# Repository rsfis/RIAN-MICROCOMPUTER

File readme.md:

<h1 align="center">
  Fiscion Razor32
</h1>
<h3 align="center">
  A Mini Foldable OldStyle Computer
</h3>

<h3 align="center">
  Being only 14x6x5cm, Razor32 is a complete computer with Firmware, OS and Apps.
</h3>

## Features
- Powered by ESP32 S3 Chip with 8mb RAM and 16mb Flash
- Embedded TFT Screen
- 30 keys Matricial Keyboard. Each key has X and Y push up output
- 3000mah Rechargeable Battery
- Foldable Case Easy and Light to Carry
- USB C charging port
- Easy to assemble
- Custom Firmware and OS
- Runs LUA for Apps
- Easy to create your own apps in a Inside IDE and share them within a local network

## Case
Designed using Blender, the Case comes with 4 parts: The lower box, upper box, hinges and screws. Made using PLA material.

## PCB
The PCBs were made using KiCad. The board contains the sockets for esp32 and screen and a 3x10 matricial keyboard using push buttons.

F.Cu

In.1.Cu

In.2.Cu

B.Cu

3D render front

3D render back

Schematic

#### External Wiring Diagram

## BOM
|FIELD1|Designator                                  |Quantity|Comment                                                                                                       |Link                                                                                                                                       |ENTIRE PRICE WITH FREIGHT AND TAXES:|FIELD7|FIELD8|FIELD9|
|------|--------------------------------------------|--------|--------------------------------------------------------------------------------------------------------------|-------------------------------------------------------------------------------------------------------------------------------------------|------------------------------------|------|------|------|
|1     |TFT Screen 3.5" st7796 320*480 ips          |1       |TFT Screen 3.5" st7796 320*480 ips Touch                                                                      |https://pt.aliexpress.com/item/1005005995931721.html?spm=a2g0o.order_list.order_list_main.31.288ecaa4EGynx2&gatewayAdapt=glo2bra           |R$ 90,84                            |      |      |      |
|2     |ESP32 S3 8mb PSRAM 16mb Flash               |1       |ESP32-S3-DevKitC-1                                                                                            |https://pt.aliexpress.com/item/1005007215982839.html?spm=a2g0o.order_list.order_list_main.46.288ecaa4EGynx2&gatewayAdapt=glo2bra           |R$ 63,38                            |      |      |      |
|3     |Aliexpress parts                            |1       |Pin Headers 1x15 and 1x6; Flat Cable Socket Bottom Connector 14pins; Screws M3x6mm Allen; Push Buttons 6x6x5mm|(Cart image at repo: cart/aliexpress.png)                                                                                                  |R$ 129,76                           |      |      |      |
|4     |3D Print                                    |2       |3D Print Case                                                                                                 |~                                                                                                                                          |~                                   |      |      |      |
|5     |PCB                                         |5       |PCB Manufacture Process                                                                                       |~                                                                                                                                          |$36,35                              |      |      |PRICE |
|6     |Battery 3.7v 3000mah                        |1       |Battery 3000mah 3.7v                                                                                          |https://www.mercadolivre.com.br/1-unidade-505573-2-fios-3000mah-37v-5mm-x-55mm-x-73mm/p/MLB2081347995?pdp_filters=item_id:MLB1929447427    |$12,00                              |      |R$    |552,13|
|7     |Battery Charger Module and Step Up Conversor|1       |Battery Charger Module and Step Up 3.7v to 5v Conversor                                                       |https://www.mercadolivre.com.br/carregador-bateria-de-litio-5v-2a-conversor-step-up-usb-c/p/MLB2071876811?pdp_filters=item_id:MLB4418035779|$3,42                               |      |USD   |106,59|

## Keyboard Keys Organization
q w e r t y u i o p

a s d f g h j k l B

z x c v b S n m f E

1 2 3 4 5 6 7 8 9 0

+ - % < > ? & ! ( )

/ * = " _ ; . , f Sh

ESC F1 F2 F3 F4 F5 F6 F7 F8 F9

{    }  @ :  [  ]  

|    \  ' -  HOME

## OS and APPS
The OS is the RazorOS, made using ArduinoIDE, LovyanGFX and LUA Interpreter.

The OS itself is programmed in C++ using Arduino IDE, with own firmware. The OS has:
- Home Page with a Desktop area
- Control Panel for Rapid Settings
- Users
- Clock
- Settings
- Task Manager
- Notifications
- Watchdog
- Terminal in LUA

The apps are made in LUA. Apps will create a LUA Virtual Machine to execute the code directly in the processor using various C++ External Functions. 

Using the Text Editor, you will also be able to create your own apps to Razor32 and control everything.

Planned Apps:
- Internet Browser Based on Text (Lynx)
- File Sender

- Text Editor
- Calculator
- To-do
- Calendar
- PDF Viewer
- Excel Like

- Tetris
- Snake

- Scanner Wifi
- Terminal Serial
- Packet Logger

OS and Firmware are still being programmed. For now, RazorOS already has basic drawing and OS functions and Lua VM implemented.

## Cart

## Getting Started
### How to flash the ESP32:
- Install ArduinoIDE
- Install the following libraries:
-- LovyanGFX, by lovyan03
-- ArduinoJSON, by BenoitBlanchon
- Install the following Board Managers:
-- esp32, by Espressif Systems
-- Select the COM and board 4D Systems gen4-ESP32 Modules (ESP32-S3)
### Extract the files from /firmware/MicroSD Backup.rar
- Copy the files from /firmware/MicroSD Backup.rar to the microsd root directory
- Insert the micro sd in the MicroSD socket below the screen

Made for: Hackclub FORGE - https://forge.hackclub.com/projects/457

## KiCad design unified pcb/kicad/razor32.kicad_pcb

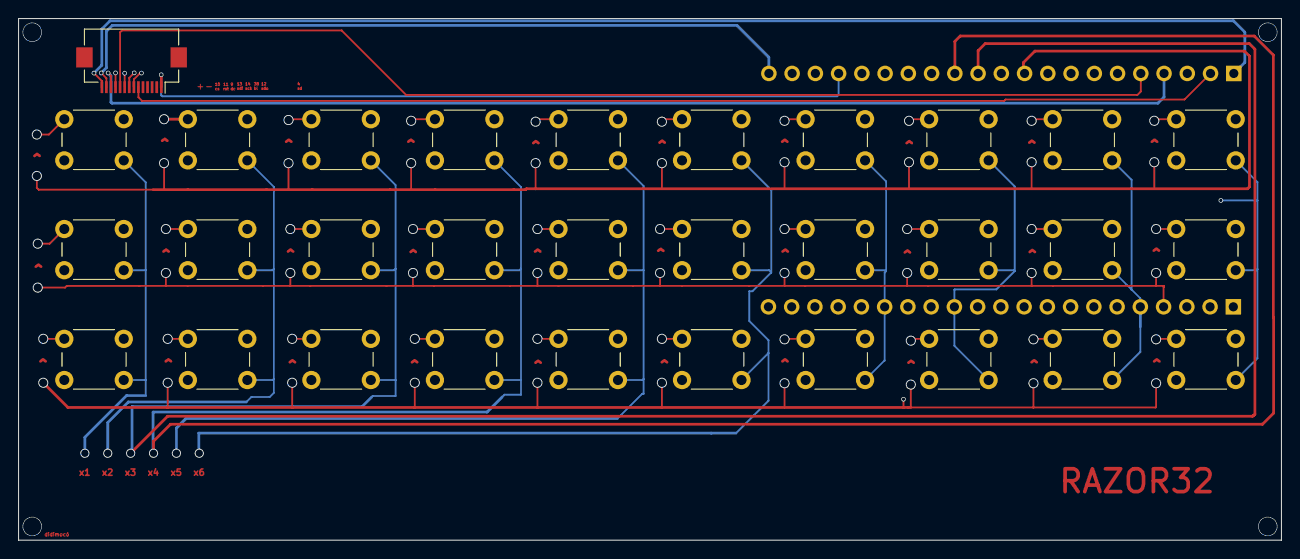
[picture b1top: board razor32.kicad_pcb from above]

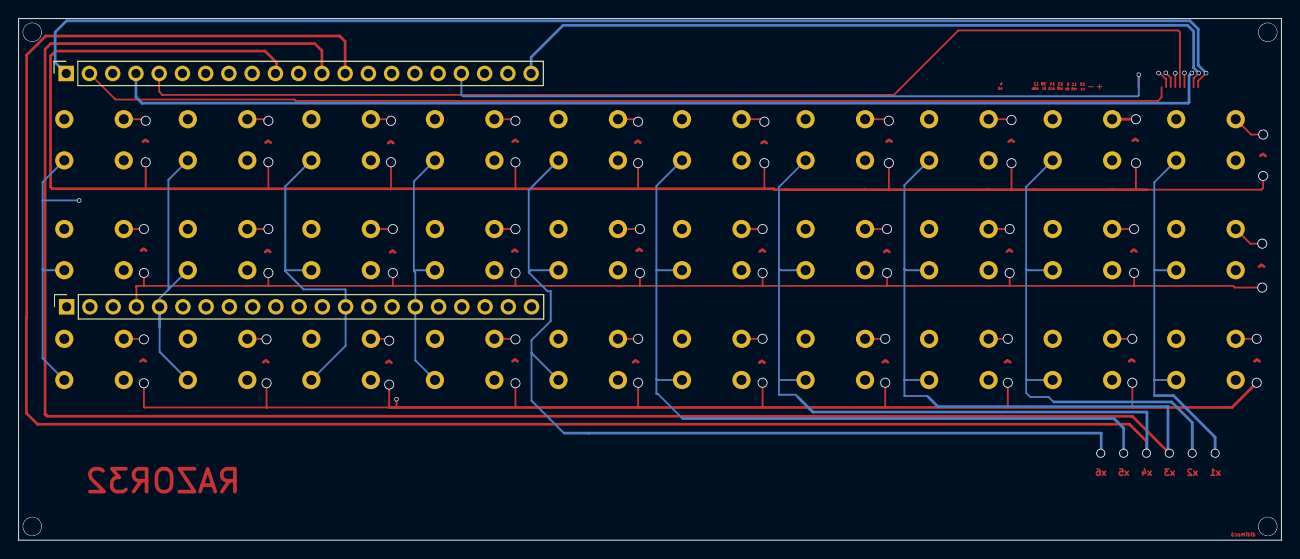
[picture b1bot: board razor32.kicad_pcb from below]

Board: 4 copper layers, 138.0 x 57.0 mm, 33 parts (2 on the bottom side), 23 nets.

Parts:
ESP32PinSocket_1, ESP32PinSocket_2: PinSocket_1x21_P2.54mm_Vertical
FlatCableSocket: Hirose_FH12-14S-0.5SH_1x14-1MP_P0.50mm_Horizontal
a: SW_PUSH_6mm
b: SW_PUSH_6mm
c: SW_PUSH_6mm
d: SW_PUSH_6mm
e: SW_PUSH_6mm
enter: SW_PUSH_6mm
f: SW_PUSH_6mm
fun: SW_PUSH_6mm
g: SW_PUSH_6mm
h: SW_PUSH_6mm
i: SW_PUSH_6mm
j: SW_PUSH_6mm
k: SW_PUSH_6mm
l: SW_PUSH_6mm
m: SW_PUSH_6mm
n: SW_PUSH_6mm
o: SW_PUSH_6mm
p: SW_PUSH_6mm
q: SW_PUSH_6mm
r: SW_PUSH_6mm
ret: SW_PUSH_6mm
s: SW_PUSH_6mm
space: SW_PUSH_6mm
t: SW_PUSH_6mm
u: SW_PUSH_6mm
v: SW_PUSH_6mm
w: SW_PUSH_6mm
x: SW_PUSH_6mm
y: SW_PUSH_6mm
z: SW_PUSH_6mm

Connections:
bl: ESP32PinSocket_2.12, FlatCableSocket.7
cs: ESP32PinSocket_1.4, FlatCableSocket.12
dc: ESP32PinSocket_1.5, FlatCableSocket.10
rst: ESP32PinSocket_1.3, FlatCableSocket.11
sck: ESP32PinSocket_2.3, FlatCableSocket.8
sd: ESP32PinSocket_1.18, FlatCableSocket.1
sdi: ESP32PinSocket_2.2, FlatCableSocket.9
sdo: ESP32PinSocket_1.2, FlatCableSocket.6
sgnd: ESP32PinSocket_1.21, FlatCableSocket.13
vcc: ESP32PinSocket_1.1, FlatCableSocket.14
x1: ESP32PinSocket_2.6, a.2, q.2, z.2
x2: ESP32PinSocket_2.7, s.2, w.2, x.2
x3: ESP32PinSocket_1.12, c.2, d.2, e.2
x4: ESP32PinSocket_1.13, f.2, r.2, v.2
x5: ESP32PinSocket_2.14, b.2, g.2, t.2
x6: ESP32PinSocket_1.11, h.2, space.2, y.2
x7: ESP32PinSocket_2.16, j.2, n.2, u.2
x8: ESP32PinSocket_2.13, i.2, k.2, m.2
x9: ESP32PinSocket_2.5, fun.2, l.2, o.2
x10: ESP32PinSocket_1.15, enter.2, p.2, ret.2
y1: ESP32PinSocket_1.10, e.1, i.1, o.1, p.1, q.1, r.1, t.1, u.1, w.1, y.1
y2: ESP32PinSocket_2.4, a.1, d.1, f.1, g.1, h.1, j.1, k.1, l.1, ret.1, s.1
y3: ESP32PinSocket_2.15, b.1, c.1, enter.1, fun.1, m.1, n.1, space.1, v.1, x.1, z.1

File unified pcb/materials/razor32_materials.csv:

Id;Designator;Footprint;Quantity;Comment;JLCPCB Part #;Link
1;a;SW_PUSH_6mm;1;SW_PUSH_6mm;C97440;https://jlcpcb.com/partdetail/ALPSALPINE-SKHHAJA010/C97440
2;b;SW_PUSH_6mm;1;SW_PUSH_6mm;C97440;https://jlcpcb.com/partdetail/ALPSALPINE-SKHHAJA010/C97440
3;c;SW_PUSH_6mm;1;SW_PUSH_6mm;C97440;https://jlcpcb.com/partdetail/ALPSALPINE-SKHHAJA010/C97440
4;d;SW_PUSH_6mm;1;SW_PUSH_6mm;C97440;https://jlcpcb.com/partdetail/ALPSALPINE-SKHHAJA010/C97440
5;e;SW_PUSH_6mm;1;SW_PUSH_6mm;C97440;https://jlcpcb.com/partdetail/ALPSALPINE-SKHHAJA010/C97440
6;f;SW_PUSH_6mm;1;SW_PUSH_6mm;C97440;https://jlcpcb.com/partdetail/ALPSALPINE-SKHHAJA010/C97440
7;g;SW_PUSH_6mm;1;SW_PUSH_6mm;C97440;https://jlcpcb.com/partdetail/ALPSALPINE-SKHHAJA010/C97440
8;h;SW_PUSH_6mm;1;SW_PUSH_6mm;C97440;https://jlcpcb.com/partdetail/ALPSALPINE-SKHHAJA010/C97440
9;i;SW_PUSH_6mm;1;SW_PUSH_6mm;C97440;https://jlcpcb.com/partdetail/ALPSALPINE-SKHHAJA010/C97440
10;j;SW_PUSH_6mm;1;SW_PUSH_6mm;C97440;https://jlcpcb.com/partdetail/ALPSALPINE-SKHHAJA010/C97440
11;k;SW_PUSH_6mm;1;SW_PUSH_6mm;C97440;https://jlcpcb.com/partdetail/ALPSALPINE-SKHHAJA010/C97440
12;l;SW_PUSH_6mm;1;SW_PUSH_6mm;C97440;https://jlcpcb.com/partdetail/ALPSALPINE-SKHHAJA010/C97440
13;m;SW_PUSH_6mm;1;SW_PUSH_6mm;C97440;https://jlcpcb.com/partdetail/ALPSALPINE-SKHHAJA010/C97440
14;n;SW_PUSH_6mm;1;SW_PUSH_6mm;C97440;https://jlcpcb.com/partdetail/ALPSALPINE-SKHHAJA010/C97440
15;o;SW_PUSH_6mm;1;SW_PUSH_6mm;C97440;https://jlcpcb.com/partdetail/ALPSALPINE-SKHHAJA010/C97440
16;p;SW_PUSH_6mm;1;SW_PUSH_6mm;C97440;https://jlcpcb.com/partdetail/ALPSALPINE-SKHHAJA010/C97440
17;q;SW_PUSH_6mm;1;SW_PUSH_6mm;C97440;https://jlcpcb.com/partdetail/ALPSALPINE-SKHHAJA010/C97440
18;r;SW_PUSH_6mm;1;SW_PUSH_6mm;C97440;https://jlcpcb.com/partdetail/ALPSALPINE-SKHHAJA010/C97440
19;s;SW_PUSH_6mm;1;SW_PUSH_6mm;C97440;https://jlcpcb.com/partdetail/ALPSALPINE-SKHHAJA010/C97440
20;t;SW_PUSH_6mm;1;SW_PUSH_6mm;C97440;https://jlcpcb.com/partdetail/ALPSALPINE-SKHHAJA010/C97440
21;u;SW_PUSH_6mm;1;SW_PUSH_6mm;C97440;https://jlcpcb.com/partdetail/ALPSALPINE-SKHHAJA010/C97440
22;v;SW_PUSH_6mm;1;SW_PUSH_6mm;C97440;https://jlcpcb.com/partdetail/ALPSALPINE-SKHHAJA010/C97440
23;w;SW_PUSH_6mm;1;SW_PUSH_6mm;C97440;https://jlcpcb.com/partdetail/ALPSALPINE-SKHHAJA010/C97440
24;x;SW_PUSH_6mm;1;SW_PUSH_6mm;C97440;https://jlcpcb.com/partdetail/ALPSALPINE-SKHHAJA010/C97440
25;y;SW_PUSH_6mm;1;SW_PUSH_6mm;C97440;https://jlcpcb.com/partdetail/ALPSALPINE-SKHHAJA010/C97440
26;z;SW_PUSH_6mm;1;SW_PUSH_6mm;C97440;https://jlcpcb.com/partdetail/ALPSALPINE-SKHHAJA010/C97440
27;ret;SW_PUSH_6mm;1;SW_PUSH_6mm;C97440;https://jlcpcb.com/partdetail/ALPSALPINE-SKHHAJA010/C97440
28;enter;SW_PUSH_6mm;1;SW_PUSH_6mm;C97440;https://jlcpcb.com/partdetail/ALPSALPINE-SKHHAJA010/C97440
29;fun;SW_PUSH_6mm;1;SW_PUSH_6mm;C97440;https://jlcpcb.com/partdetail/ALPSALPINE-SKHHAJA010/C97440
30;space;SW_PUSH_6mm;1;SW_PUSH_6mm;C97440;https://jlcpcb.com/partdetail/ALPSALPINE-SKHHAJA010/C97440
31;ESP32PinSocket_1;PinSocket_1x21_P2.54mm_Vertical;1;PinSocket_1x21_P2.54mm_Vertical;C2883738;https://jlcpcb.com/partdetail/XKBConnection-X6511FV_21C85D32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
32;ESP32PinSocket_2;PinSocket_1x21_P2.54mm_Vertical;1;PinSocket_1x21_P2.54mm_Vertical;C2883738;https://jlcpcb.com/partdetail/XKBConnection-X6511FV_21C85D32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
33;FlatCableSocket;Hirose_FH12-14S-0.5SH_1x14-1MP_P0.50mm_Horizontal;1;Hirose_FH12-14S-0.5SH_1x14-1MP_P0.50mm_Horizontal;C5378715;https://jlcpcb.com/partdetail/HRS_Hirose-FH12_14S_0_5SH_55/C5378715

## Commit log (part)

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2026-01-25 Create Repository
2026-01-26 New Day
2026-01-26 A part of a new day
2026-01-26 Another Day of Work
2026-01-26 Edit design and added flat cable connector
2026-01-28 Another Day
2026-02-02 Design
2026-02-03 Removed PCB Upper
2026-02-04 Readme Added
2026-02-04 Add initial README for Rian's MicroComputer
2026-02-05 Cart and BOM updated
2026-02-05 Add subtitle to the README
2026-02-05 Update README header to HTML format
2026-02-05 Update README formatting for title and subtitle
2026-02-05 Enhance README with features and case details
    Added detailed features and case description for Rian's MicroComputer.
2026-02-05 Update product name from Rian's MicroComputer to Fiscion Razor32
2026-02-05 Added images
2026-02-06 Journal
2026-02-06 Revise readme with additional PCB and keyboard details
    Updated the readme to include PCB and keyboard sections with images.
2026-02-06 Update readme.md with new content and formatting
2026-02-06 Update readme with enhanced product details
2026-02-06 Fix HTML encoding issues in readme.md
2026-02-06 Fix HTML entities and add cart section in readme
    Updated the readme to correct HTML entities and added a new section for the cart.
2026-02-06 Wiring Diagram
2026-02-06 Updated Journal
2026-02-07 Color Pallete
2026-02-07 OS Drafts
2026-02-07 Added Schematic to PCB General
2026-02-08 Added Battery Holder to BOM and modified PCB schematic
2026-02-10 Backup
2026-02-12 Added Power Bank
2026-02-12 Corrected PCB
2026-02-12 Updated firmware and journal
2026-02-12 Updated external wiring diagram
2026-02-12 Update Wiring Diagram
2026-02-12 Updated Cart
2026-02-12 Notes for reviewer
2026-02-12 Revise README with detailed project information
    Updated the README to include new features, case design, PCB details, BOM, and OS information.
2026-02-12 Revise README for Fiscion Razor32 details
    Updated the README to include additional details about the Fiscion Razor32, its features, case design, PCB information, BOM, OS, and planned apps.
2026-02-12 Revise README for Fiscion Razor32 details
    Updated the README file to include new information about the Fiscion Razor32 computer, including features, case design, PCB details, BOM, OS, and planned apps.
2026-02-12 Revise README for Fiscion Razor32 specifications
    Updated README to include new features, specifications, and images for the Fiscion Razor32 mini computer.
2026-02-18 Update readme.md to better comprehension
2026-02-20 Added key organizations in readme
2026-02-26 Improved firmware
2026-02-27 Updated and improved firmware.
2026-02-28 Upgraded Firmware -> Lua VM for apps now accepts texts with custom fonts in binary, and also sprites rendering, wifi updates rtc.
2026-02-28 Added 2 new OS misc functions to lua vm
2026-03-01 Added GetKernelVersion exported function
2026-03-01 Update Journal
2026-03-04 Updated firmware and journal
    Made save preferences functions to the kernel and updated journal to re-review
2026-03-05 Removed unused library
2026-03-05 Improved keyboard schematic view
2026-03-05 Revise readme with updated features and OS details
    Updated the readme.md to include new features, OS details, and explaned how to install the firmware to the esp32
2026-03-05 Revise README with detailed project information
    Added the COM port and board explanation
2026-03-21 Updated cart and schematics
2026-03-22 Update powering specs
2026-03-22 Updated cart again
2026-03-22 Update cart in Readme
2026-03-22 Update case: Made the upper box close properly
2026-03-22 Update design
2026-03-27 More LUA exported functions
    Added save config and set key configs to the lua interpreter as exported functions and update journal
2026-05-18 Journal Transfer to Forge
2026-05-18 Jornal
2026-05-18 njornal
2026-05-18 Fix HTML encoding in readme.md
2026-05-18 BOM update with powerbank
2026-05-28 journal edit
2026-06-03 Added schematics to readme
    Updated readme.md to fix HTML encoding issues and improve formatting.
2026-06-03 Revise README for Fiscion Razor32 project
    Updated the README to include additional details about the Fiscion Razor32, including features, case design, PCB information, BOM, keyboard organization, OS and apps, and getting started instructions.
2026-06-05 README
2026-06-06 unified pcbs
2026-06-06 readme imgs
2026-06-07 pcb nets
2026-06-07 bom
    Updated readme.md to correct formatting and enhance clarity.
2026-06-07 cart
2026-06-18 reciepts
2026-06-18 all reciepts
